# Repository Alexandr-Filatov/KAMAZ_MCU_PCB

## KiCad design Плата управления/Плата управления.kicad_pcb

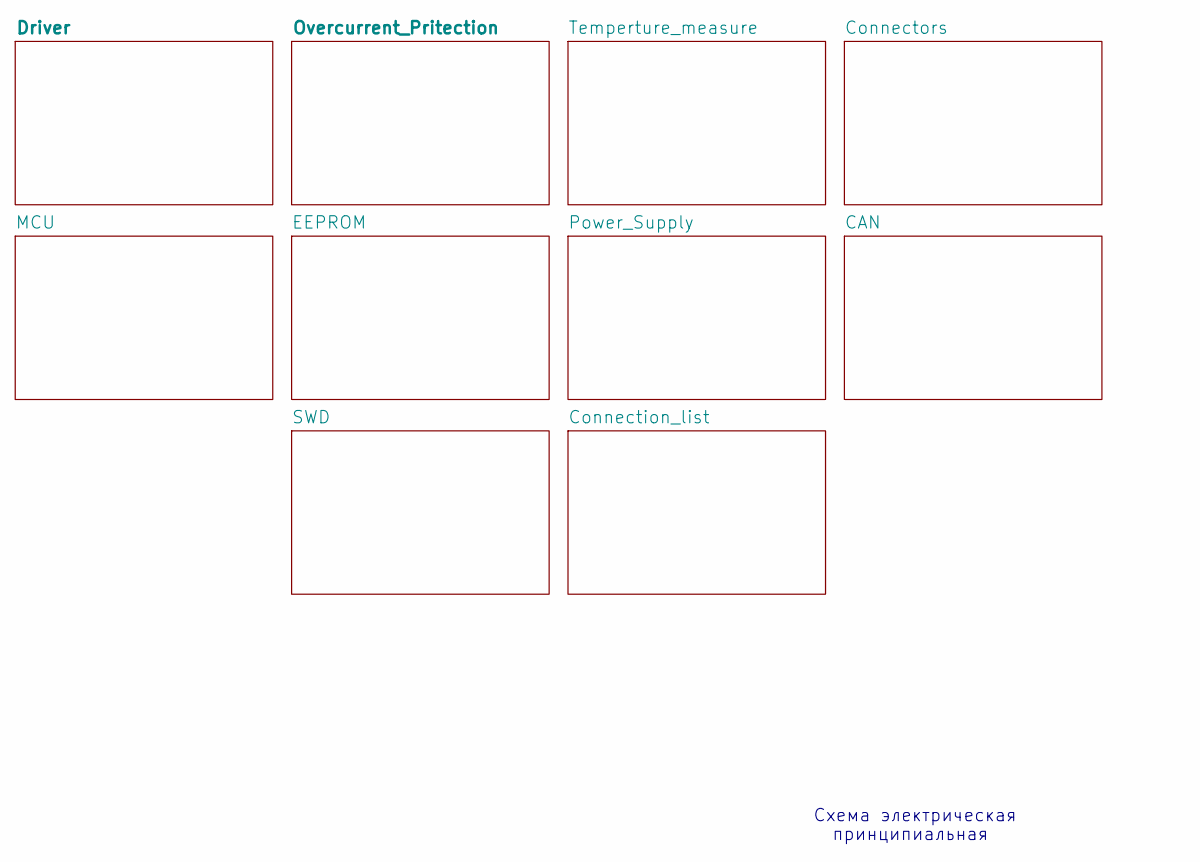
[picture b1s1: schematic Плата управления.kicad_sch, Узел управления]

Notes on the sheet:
принципиальная
Схема электрическая

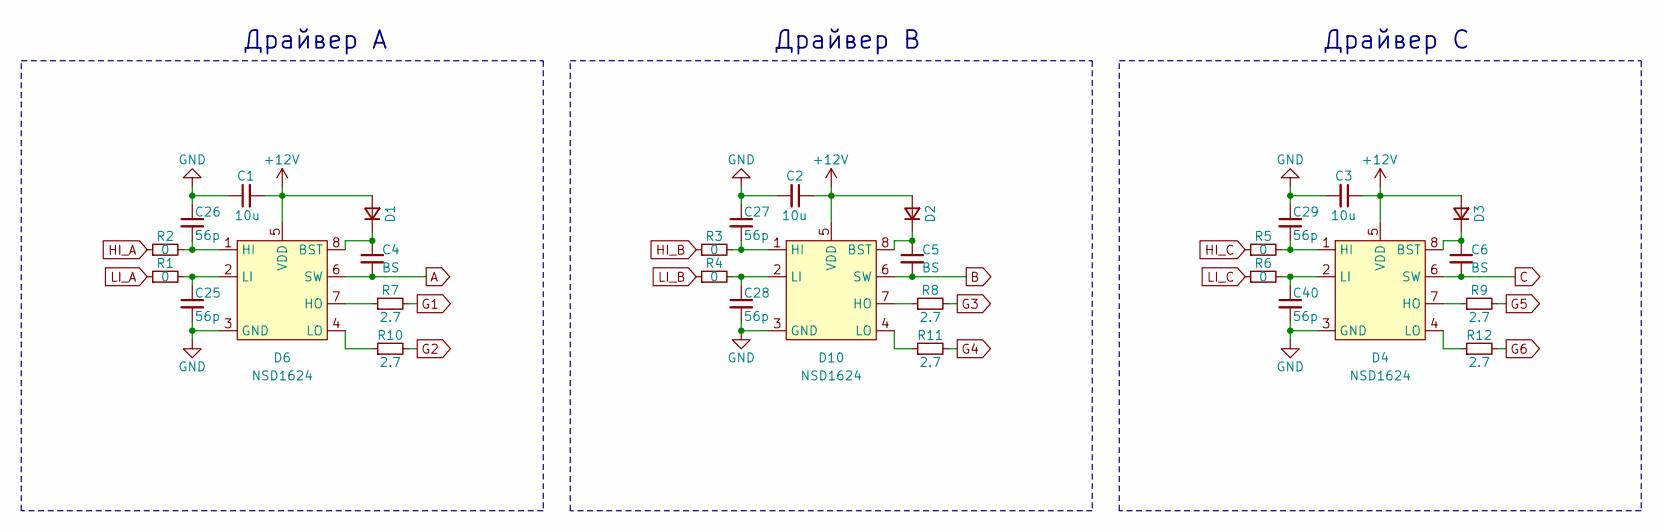
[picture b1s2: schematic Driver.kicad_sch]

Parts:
C1, C2, C3: 10u; C_0603_1608Metric_Pad1.08x0.95mm_HandSolder
C4, C5, C6: BS; C_0805_2012Metric_Pad1.18x1.45mm_HandSolder
C25, C26, C27, C28, C29, C40: 56p; C_0603_1608Metric_Pad1.08x0.95mm_HandSolder
D1, D2, D3: D_Small; D_SMA
D4, D6, D10: NSD1624; SOIC-8_3.9x4.9mm_P1.27mm
R1, R2, R3, R4, R5, R6: 0; R_0603_1608Metric_Pad0.98x0.95mm_HandSolder
R7, R8, R9, R10, R11, R12: 2.7; R_0805_2012Metric_Pad1.20x1.40mm_HandSolder

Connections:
+12V: C1.2, C2.1, C3.1, D1.2 (A), D2.2 (A), D3.2 (A), D4.5 (VDD), D6.5 (VDD), D10.5 (VDD); also elsewhere on the board
A: C4.2, D6.6 (SW); also elsewhere on the board
B: C5.2, D10.6 (SW); also elsewhere on the board
C: C6.2, D4.6 (SW); also elsewhere on the board
G1: R7.2; also elsewhere on the board
G2: R10.2; also elsewhere on the board
G3: R8.2; also elsewhere on the board
G4: R11.2; also elsewhere on the board
G5: R9.2; also elsewhere on the board
G6: R12.2; also elsewhere on the board
GND: C1.1, C2.2, C3.2, C25.2, C26.1, C27.1, C28.2, C29.1, C40.2, D4.3 (GND), D6.3 (GND), D10.3 (GND); also elsewhere on the board
HI_A: R2.1; also elsewhere on the board
HI_B: R3.1; also elsewhere on the board
HI_C: R5.1; also elsewhere on the board
LI_A: R1.1; also elsewhere on the board
LI_B: R4.1; also elsewhere on the board
LI_C: R6.1; also elsewhere on the board
unnamed: C4.1, D1.1 (K), D6.8 (BST)
unnamed: C6.1, D3.1 (K), D4.8 (BST)
unnamed: C29.2, D4.1 (HI), R5.2
unnamed: D4.7 (HO), R9.1
unnamed: C40.1, D4.2 (LI), R6.2
unnamed: D4.4 (LO), R12.1
unnamed: C26.2, D6.1 (HI), R2.2
unnamed: D6.7 (HO), R7.1
unnamed: C25.1, D6.2 (LI), R1.2
unnamed: D6.4 (LO), R10.1
unnamed: C5.1, D2.1 (K), D10.8 (BST)
unnamed: C27.2, D10.1 (HI), R3.2
unnamed: D10.7 (HO), R8.1
unnamed: C28.1, D10.2 (LI), R4.2
unnamed: D10.4 (LO), R11.1

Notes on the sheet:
Драйвер С
Драйвер А
Драйвер В

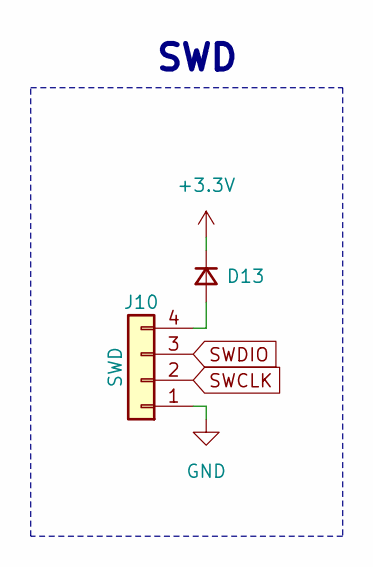
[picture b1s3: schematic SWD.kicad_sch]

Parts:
D13: D_Small; D_SOD-323_HandSoldering
J10: SWD; PinHeader_1x04_P2.54mm_Vertical

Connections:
+3.3V: D13.1 (K); also elsewhere on the board
GND: J10.1; also elsewhere on the board
unnamed: D13.2 (A), J10.4
SWCLK: J10.2; also elsewhere on the board
SWDIO: J10.3; also elsewhere on the board

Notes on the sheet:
SWD

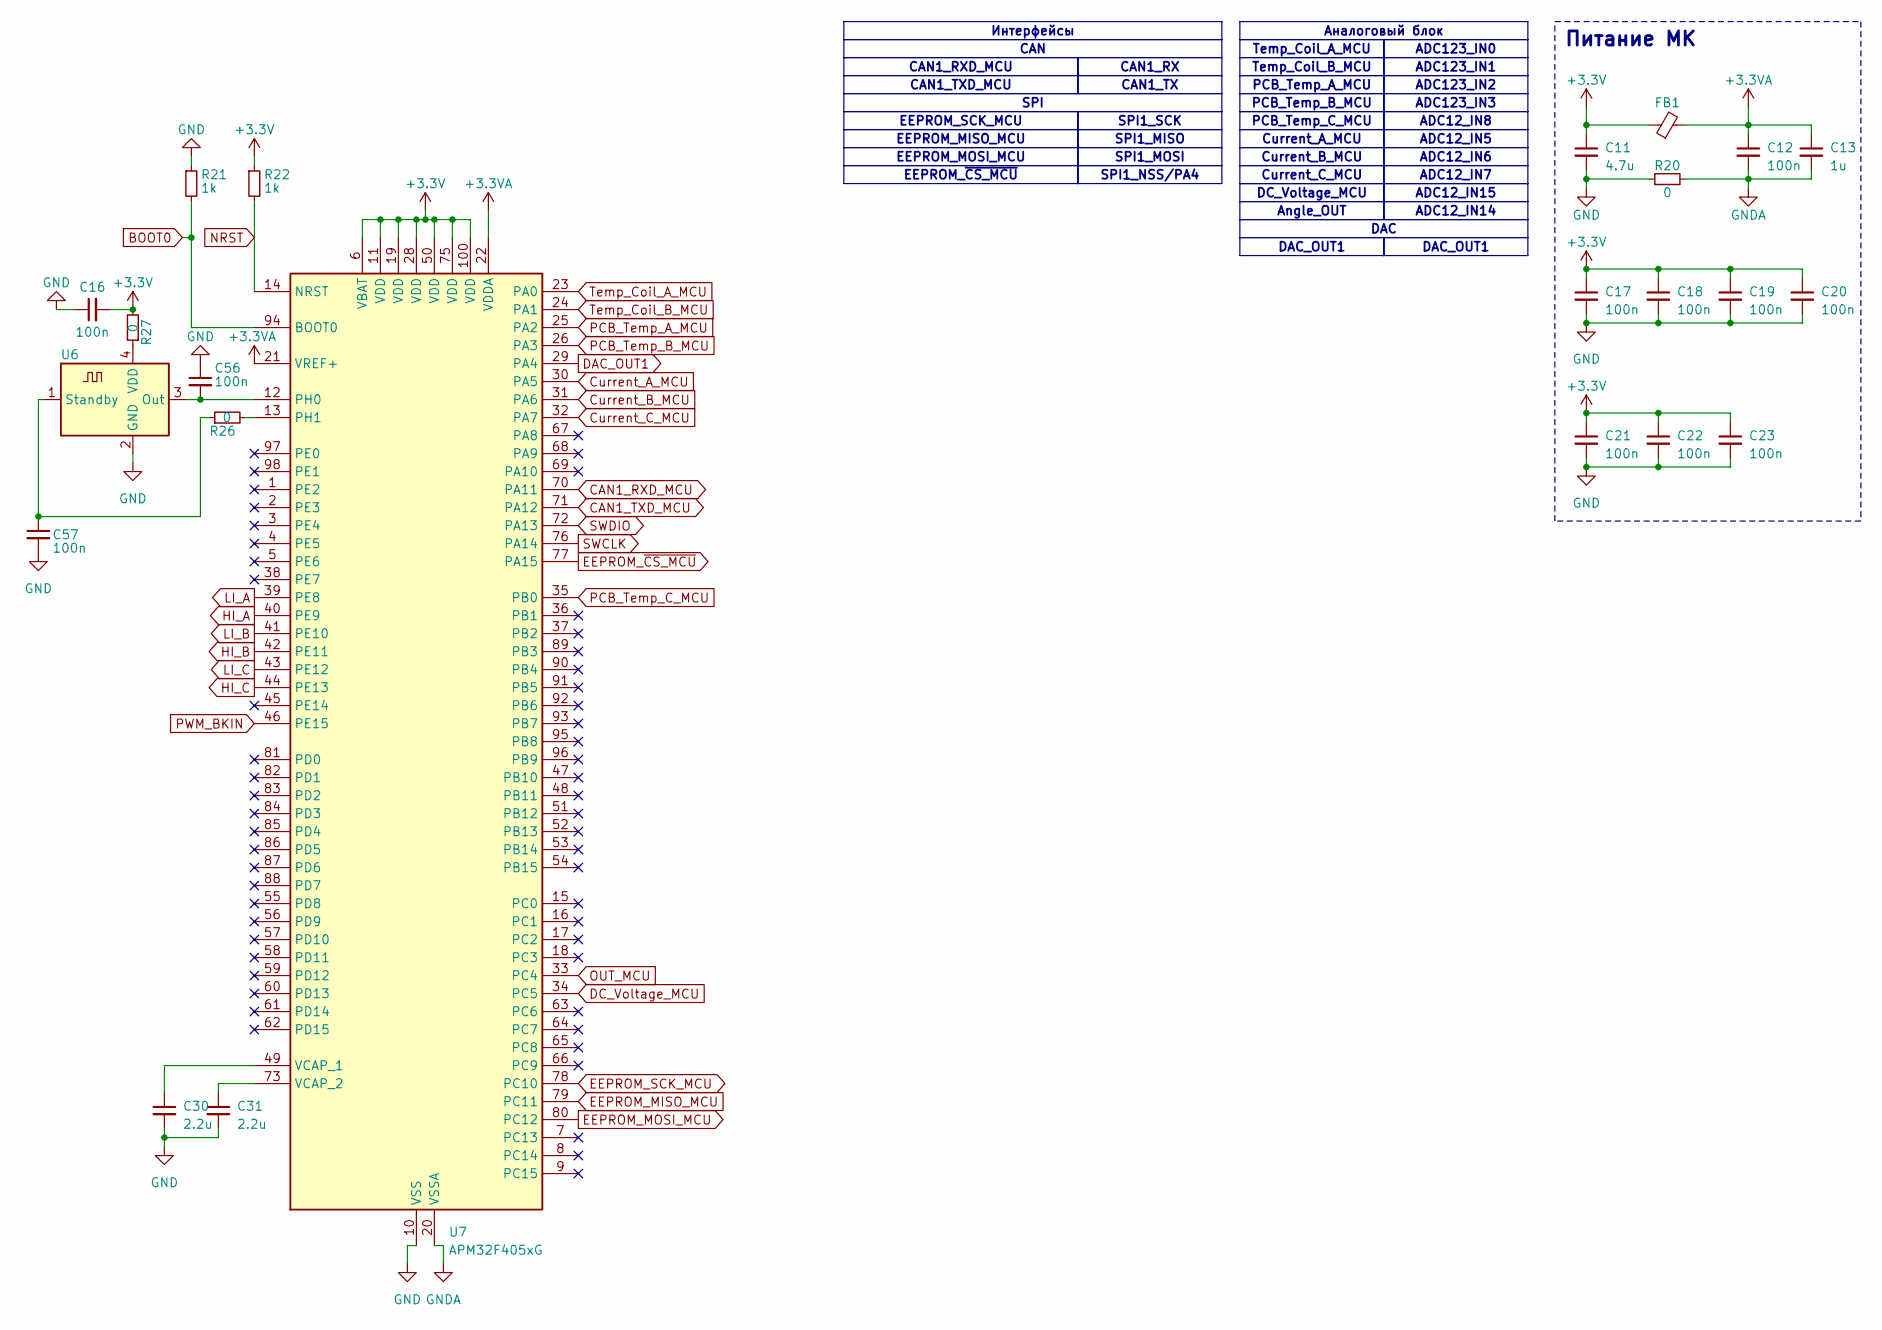
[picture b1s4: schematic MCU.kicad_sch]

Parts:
C11: 4.7u; C_0603_1608Metric_Pad1.08x0.95mm_HandSolder
C12, C16, C17, C18, C19, C20, C21, C22, C23, C56, C57: 100n; C_0603_1608Metric_Pad1.08x0.95mm_HandSolder
C13: 1u; C_0603_1608Metric_Pad1.08x0.95mm_HandSolder
C30, C31: 2.2u; C_0603_1608Metric_Pad1.08x0.95mm_HandSolder
FB1: BLM18KG102SH1D; L_0603_1608Metric_Pad1.05x0.95mm_HandSolder
R20, R26, R27: 0; R_0603_1608Metric_Pad0.98x0.95mm_HandSolder
R21, R22: 1k; R_0603_1608Metric_Pad0.98x0.95mm_HandSolder
U6: ASEMB-10; Oscillator_SMD_Abracon_ASE-4Pin_3.2x2.5mm_HandSoldering
U7: APM32F405xG; LQFP-100_14x14mm_P0.5mm

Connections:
+3.3V: C11.1, C16.2, C17.1, C18.1, C19.1, C20.1, C21.1, C22.1, C23.1, FB1.1, R22.1, R27.2, U7.6 (VBAT), U7.11 (VDD), U7.19 (VDD), U7.28 (VDD), U7.50 (VDD), U7.75 (VDD), U7.100 (VDD); also elsewhere on the board
BOOT0: R21.2, U7.94 (BOOT0)
CAN1_RXD_MCU: U7.70 (PA11); also elsewhere on the board
CAN1_TXD_MCU: U7.71 (PA12); also elsewhere on the board
Current_A_MCU: U7.30 (PA5); also elsewhere on the board
Current_B_MCU: U7.31 (PA6); also elsewhere on the board
Current_C_MCU: U7.32 (PA7); also elsewhere on the board
DAC_OUT1: U7.29 (PA4)
DC_Voltage_MCU: U7.34 (PC5); also elsewhere on the board
EEPROM_MISO_MCU: U7.79 (PC11); also elsewhere on the board
EEPROM_MOSI_MCU: U7.80 (PC12); also elsewhere on the board
EEPROM_SCK_MCU: U7.78 (PC10); also elsewhere on the board
EEPROM_~CS_MCU: U7.77 (PA15); also elsewhere on the board
GND: C11.2, C16.1, C17.2, C18.2, C19.2, C20.2, C21.2, C22.2, C23.2, C30.2, C31.2, C56.1, C57.2, R20.1, R21.1, U6.2 (GND), U7.10 (VSS), U7.27 (VSS), U7.74 (VSS), U7.99 (VSS); also elsewhere on the board
GNDA: C12.2, C13.2, R20.2, U7.20 (VSSA); also elsewhere on the board
HI_A: U7.40 (PE9); also elsewhere on the board
HI_B: U7.42 (PE11); also elsewhere on the board
HI_C: U7.44 (PE13); also elsewhere on the board
LI_A: U7.39 (PE8); also elsewhere on the board
LI_B: U7.41 (PE10); also elsewhere on the board
LI_C: U7.43 (PE12); also elsewhere on the board
NRST: R22.2, U7.14 (NRST)
NTC_A+: C12.1, C13.1, FB1.2, U7.21 (VREF+), U7.22 (VDDA); also elsewhere on the board
unnamed: C56.2, U6.3 (Out), U7.12 (PH0)
unnamed: C57.1, R26.1, U6.1 (Standby)
unnamed: R27.1, U6.4 (VDD)
unnamed: R26.2, U7.13 (PH1)
unnamed: C30.1, U7.49 (VCAP_1)
unnamed: C31.1, U7.73 (VCAP_2)
OUT_MCU: U7.33 (PC4); also elsewhere on the board
PCB_Temp_A_MCU: U7.25 (PA2); also elsewhere on the board
PCB_Temp_B_MCU: U7.26 (PA3); also elsewhere on the board
PCB_Temp_C_MCU: U7.35 (PB0); also elsewhere on the board
PWM_BKIN: U7.46 (PE15); also elsewhere on the board
SWCLK: U7.76 (PA14); also elsewhere on the board
SWDIO: U7.72 (PA13); also elsewhere on the board
Temp_Coil_A_MCU: U7.23 (PA0); also elsewhere on the board
Temp_Coil_B_MCU: U7.24 (PA1); also elsewhere on the board

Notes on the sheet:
EEPROM_MOSI_MCU
SPI1_MOSI
Angle_OUT
ADC123_IN0
DAC_OUT1
ADC12_IN15
CAN1_RXD_MCU
SPI1_MISO
CAN1_TX
SPI1_NSS/PA4
DC_Voltage_MCU
ADC12_IN5
EEPROM_~{CS_MCU}
ADC123_IN2
Current_C_MCU
CAN1_TXD_MCU
EEPROM_MISO_MCU
PCB_Temp_A_MCU
PCB_Temp_C_MCU
DAC
Temp_Coil_B_MCU
ADC12_IN14
Current_A_MCU
CAN
ADC12_IN6
Temp_Coil_A_MCU
ADC12_IN7
Аналоговый блок
SPI1_SCK
ADC123_IN3
ADC12_IN8
EEPROM_SCK_MCU
SPI
Current_B_MCU
CAN1_RX
PCB_Temp_B_MCU
ADC123_IN1
Интерфейсы
Питание МК

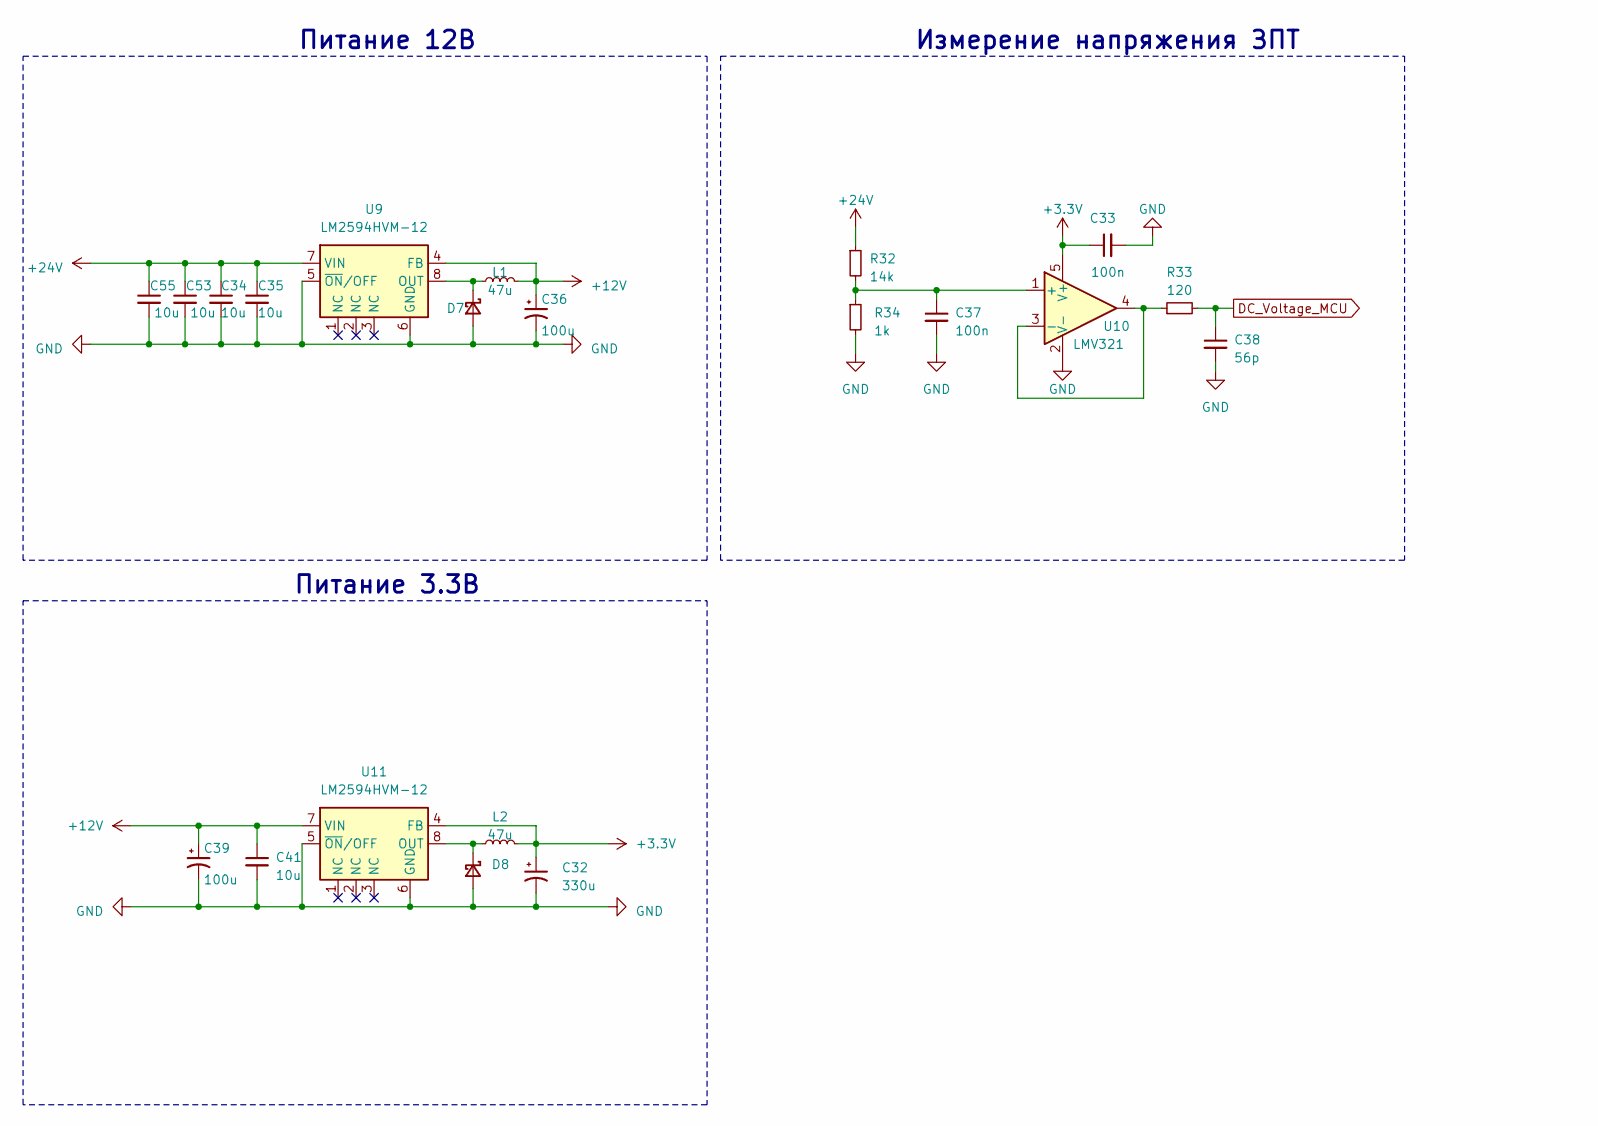
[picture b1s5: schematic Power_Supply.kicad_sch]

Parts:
C32: 330u; CP_EIA-7343-31_Kemet-D_Pad2.25x2.55mm_HandSolder
C33, C37: 100n; C_0603_1608Metric_Pad1.08x0.95mm_HandSolder
C34, C35, C41, C53, C55: 10u; C_1210_3225Metric_Pad1.33x2.70mm_HandSolder
C36, C39: 100u; CP_EIA-7343-43_Kemet-X_Pad2.25x2.55mm_HandSolder
C38: 56p; C_0603_1608Metric_Pad1.08x0.95mm_HandSolder
D7, D8: MBRA320; D_SMA
L1, L2: 47u; C_2220_5650Metric_Pad1.97x5.40mm_HandSolder
R32: 14k; R_0603_1608Metric_Pad0.98x0.95mm_HandSolder
R33: 120; R_0603_1608Metric_Pad0.98x0.95mm_HandSolder
R34: 1k; R_0603_1608Metric_Pad0.98x0.95mm_HandSolder
U9, U11: LM2594HVM-12; SOIC-8_3.9x4.9mm_P1.27mm
U10: LMV321; SOT-23-5_HandSoldering

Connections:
+3.3V: C32.1, C33.1, L2.2, U10.5 (V+), U11.4 (FB); also elsewhere on the board
+12V: C36.1, C39.1, C41.1, L1.2, U9.4 (FB), U11.7 (VIN); also elsewhere on the board
+24V: C34.1, C35.1, C53.1, C55.1, R32.1, U9.7 (VIN); also elsewhere on the board
DC_Voltage_MCU: C38.1, R33.2; also elsewhere on the board
GND: C32.2, C33.2, C34.2, C35.2, C36.2, C37.2, C38.2, C39.2, C41.2, C53.2, C55.2, D7.2 (A), D8.2 (A), R34.2, U9.5 (~ON/OFF), U9.6 (GND), U10.2 (V-), U11.5 (~ON/OFF), U11.6 (GND); also elsewhere on the board
unnamed: D7.1 (K), L1.1, U9.8 (OUT)
unnamed: D8.1 (K), L2.1, U11.8 (OUT)
unnamed: C37.1, R32.2, R34.1, U10.1 (+)
unnamed: R33.1, U10.3 (-), U10.4

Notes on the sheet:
Питание 3.3В
Измерение напряжения ЗПТ
Питание 12В

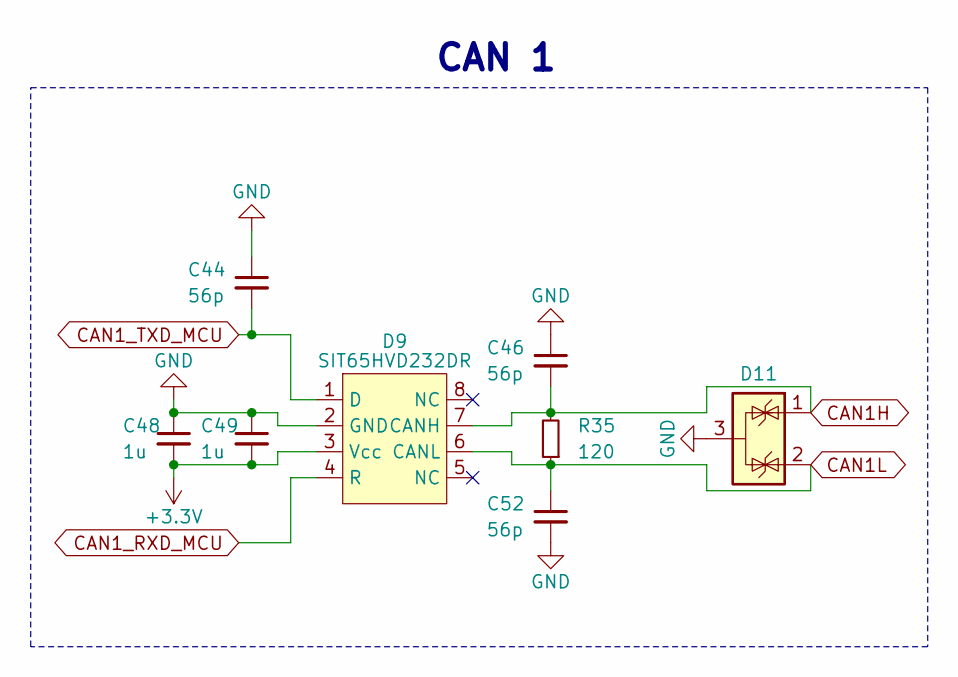
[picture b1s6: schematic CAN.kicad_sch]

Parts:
C44, C46, C52: 56p; C_0603_1608Metric_Pad1.08x0.95mm_HandSolder
C48, C49: 1u; C_0603_1608Metric_Pad1.08x0.95mm_HandSolder
D9: SIT65HVD232DR; SOIC-8_3.9x4.9mm_P1.27mm
D11: PESD2CAN; SOT-23
R35: 120; R_0603_1608Metric_Pad0.98x0.95mm_HandSolder

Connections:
+3.3V: C48.2, C49.2, D9.3 (Vcc); also elsewhere on the board
CAN1H: C46.2, D9.7 (CANH), D11.1 (K), R35.2; also elsewhere on the board
CAN1L: C52.1, D9.6 (CANL), D11.2 (K), R35.1; also elsewhere on the board
CAN1_RXD_MCU: D9.4 (R); also elsewhere on the board
CAN1_TXD_MCU: C44.2, D9.1 (D); also elsewhere on the board
GND: C44.1, C46.1, C48.1, C49.1, C52.2, D9.2 (GND), D11.3 (A); also elsewhere on the board

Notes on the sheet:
CAN 1

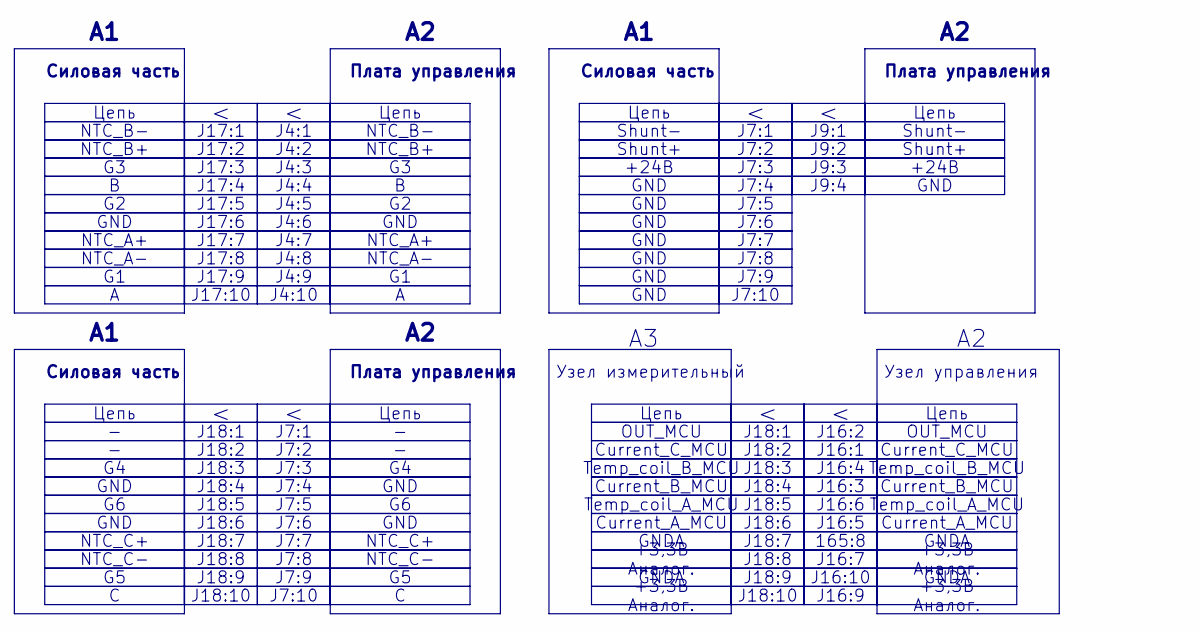
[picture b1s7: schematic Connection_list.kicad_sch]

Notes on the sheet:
GND
J16:4
GNDA
J7:10
J18:2
J7:6
J7:6
J18:8
Temp_coil_B_MCU
J7:4
Shunt+
J18:7
J17:8
J4:6
NTC_C+
J7:3
Цепь
J7:1
J16:7
+24В
J18:10
J7:9
J18:3
J7:7
OUT_MCU
J7:3
J18:8
NTC_B-
J18:4
J7:7
J18:6
NTC_A+
J9:3
Shunt-
+3,3В Аналог.
J4:10
Temp_coil_A_MCU
J18:3
J18:1
J7:2

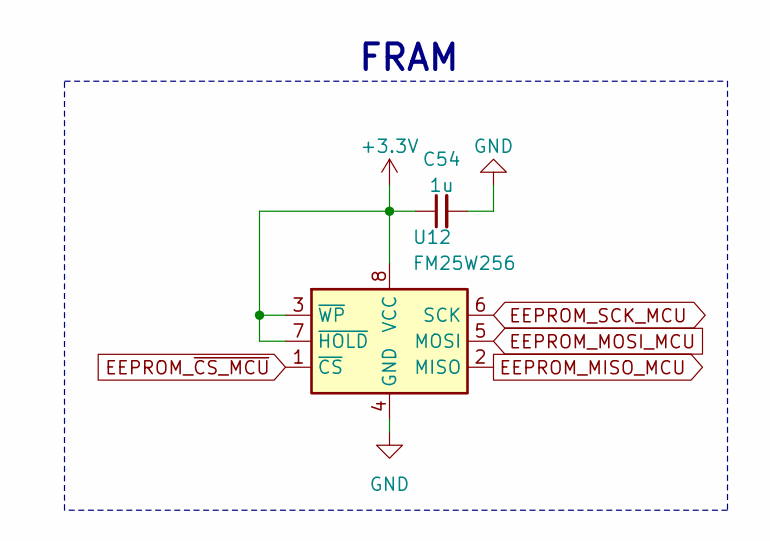
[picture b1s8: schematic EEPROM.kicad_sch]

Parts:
C54: 1u; C_0603_1608Metric_Pad1.08x0.95mm_HandSolder
U12: FM25W256; SOIC-8_3.9x4.9mm_P1.27mm

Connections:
+3.3V: C54.1, U12.3 (~WP), U12.7 (~HOLD), U12.8 (VCC); also elsewhere on the board
EEPROM_MISO_MCU: U12.2 (MISO); also elsewhere on the board
EEPROM_MOSI_MCU: U12.5 (MOSI); also elsewhere on the board
EEPROM_SCK_MCU: U12.6 (SCK); also elsewhere on the board
EEPROM_~CS_MCU: U12.1 (~CS); also elsewhere on the board
GND: C54.2, U12.4 (GND); also elsewhere on the board

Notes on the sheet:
FRAM

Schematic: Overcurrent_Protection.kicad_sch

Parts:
C7, C8: 100n; C_0603_1608Metric_Pad1.08x0.95mm_HandSolder
C9, C10: 56p; C_0603_1608Metric_Pad1.08x0.95mm_HandSolder
R13: 649; R_0603_1608Metric_Pad0.98x0.95mm_HandSolder
R14: 1k; R_0603_1608Metric_Pad0.98x0.95mm_HandSolder
R15, R16: 120; R_0603_1608Metric_Pad0.98x0.95mm_HandSolder
U4: LMV7239M5; SOT-23-5_HandSoldering
U5: AD8418A; SOIC-8_3.9x4.9mm_P1.27mm

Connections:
+3.3V: C7.1, C8.1, R13.1, U4.5 (V+), U5.6 (V+); also elsewhere on the board
GND: C7.2, C8.2, C9.2, C10.2, R14.2, U4.2 (V-), U5.2 (GND), U5.3 (REF2), U5.7 (REF1); also elsewhere on the board
unnamed: R15.1, U4.1
unnamed: R16.2, U5.5
unnamed: C10.1, R16.1, U4.3 (+)
unnamed: R13.2, R14.1, U4.4 (-)
PWM_BKIN: C9.1, R15.2; also elsewhere on the board
Shunt+: U5.8 (+); also elsewhere on the board
Shunt-: U5.1 (-); also elsewhere on the board

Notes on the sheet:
Защита от КЗ

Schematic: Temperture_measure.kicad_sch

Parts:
C14, C24, C42, C43, C47, C50: 100n; C_0603_1608Metric_Pad1.08x0.95mm_HandSolder
C15, C45, C51: 56p; C_0603_1608Metric_Pad1.08x0.95mm_HandSolder
R17, R18, R19: 120; R_0603_1608Metric_Pad0.98x0.95mm_HandSolder
R23, R24, R25: 10k; R_0603_1608Metric_Pad0.98x0.95mm_HandSolder
U1, U2, U8: LMV321; SOT-23-5_HandSoldering

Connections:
GNDA: C14.1, C15.2, C24.2, C42.1, C43.2, C45.2, C47.1, C50.2, C51.2, R23.1, R24.1, R25.1, U1.2 (V-), U2.2 (V-), U8.2 (V-); also elsewhere on the board
NTC_A+: C24.1, C43.1, C50.1, U1.5 (V+), U2.5 (V+), U8.5 (V+); also elsewhere on the board
NTC_A-: C14.2, R23.2, U8.1 (+); also elsewhere on the board
NTC_B-: C42.2, R24.2, U1.1 (+); also elsewhere on the board
NTC_C-: C47.2, R25.2, U2.1 (+); also elsewhere on the board
unnamed: R18.1, U1.3 (-), U1.4
unnamed: R19.1, U2.3 (-), U2.4
unnamed: R17.1, U8.3 (-), U8.4
PCB_Temp_A_MCU: C15.1, R17.2; also elsewhere on the board
PCB_Temp_B_MCU: C45.1, R18.2; also elsewhere on the board
PCB_Temp_C_MCU: C51.1, R19.2; also elsewhere on the board

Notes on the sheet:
Температура силовой платы A
Температура силовой платы B
Температура силовой платы C

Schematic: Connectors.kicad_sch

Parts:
J1: A; Hole_9mm
J2: B; Hole_9mm
J3: C; Hole_9mm
J4, J7: Conn_01x10; PinHeader_1x10_P1.27mm_Vertical
J5, J11, J12, J13, J14, J15: C; Wire_one
J6, J8: Conn_01x02; PinHeader_1x02_P1.27mm_Vertical
J9: Conn_01x04; PinHeader_1x04_P1.27mm_Vertical
J16: Conn_02x05_Odd_Even; PinHeader_2x05_P1.27mm_Vertical

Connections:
+24V: J9.3; also elsewhere on the board
A: J4.10; also elsewhere on the board
B: J4.4; also elsewhere on the board
C: J7.10; also elsewhere on the board
CAN1H: J5.1, J13.1; also elsewhere on the board
CAN1L: J11.1, J14.1; also elsewhere on the board
Current_A_MCU: J16.5; also elsewhere on the board
Current_B_MCU: J16.3; also elsewhere on the board
Current_C_MCU: J16.1; also elsewhere on the board
G1: J4.9; also elsewhere on the board
G2: J4.5; also elsewhere on the board
G3: J4.3; also elsewhere on the board
G4: J7.3; also elsewhere on the board
G5: J7.9; also elsewhere on the board
G6: J7.5; also elsewhere on the board
GND: J4.6, J7.4, J7.6, J9.4, J12.1, J15.1; also elsewhere on the board
GNDA: J16.8, J16.10; also elsewhere on the board
NTC_A+: J4.2, J4.7, J7.7, J16.7, J16.9; also elsewhere on the board
NTC_A-: J4.8; also elsewhere on the board
NTC_B-: J4.1; also elsewhere on the board
NTC_C-: J7.8; also elsewhere on the board
OUT_MCU: J16.2; also elsewhere on the board
Shunt+: J9.2; also elsewhere on the board
Shunt-: J9.1; also elsewhere on the board
Temp_Coil_A_MCU: J16.6; also elsewhere on the board
Temp_Coil_B_MCU: J16.4; also elsewhere on the board

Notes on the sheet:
Фазные разъёмы
Разъём платы датчиков
Наружний разъём
Разъём платы силовой

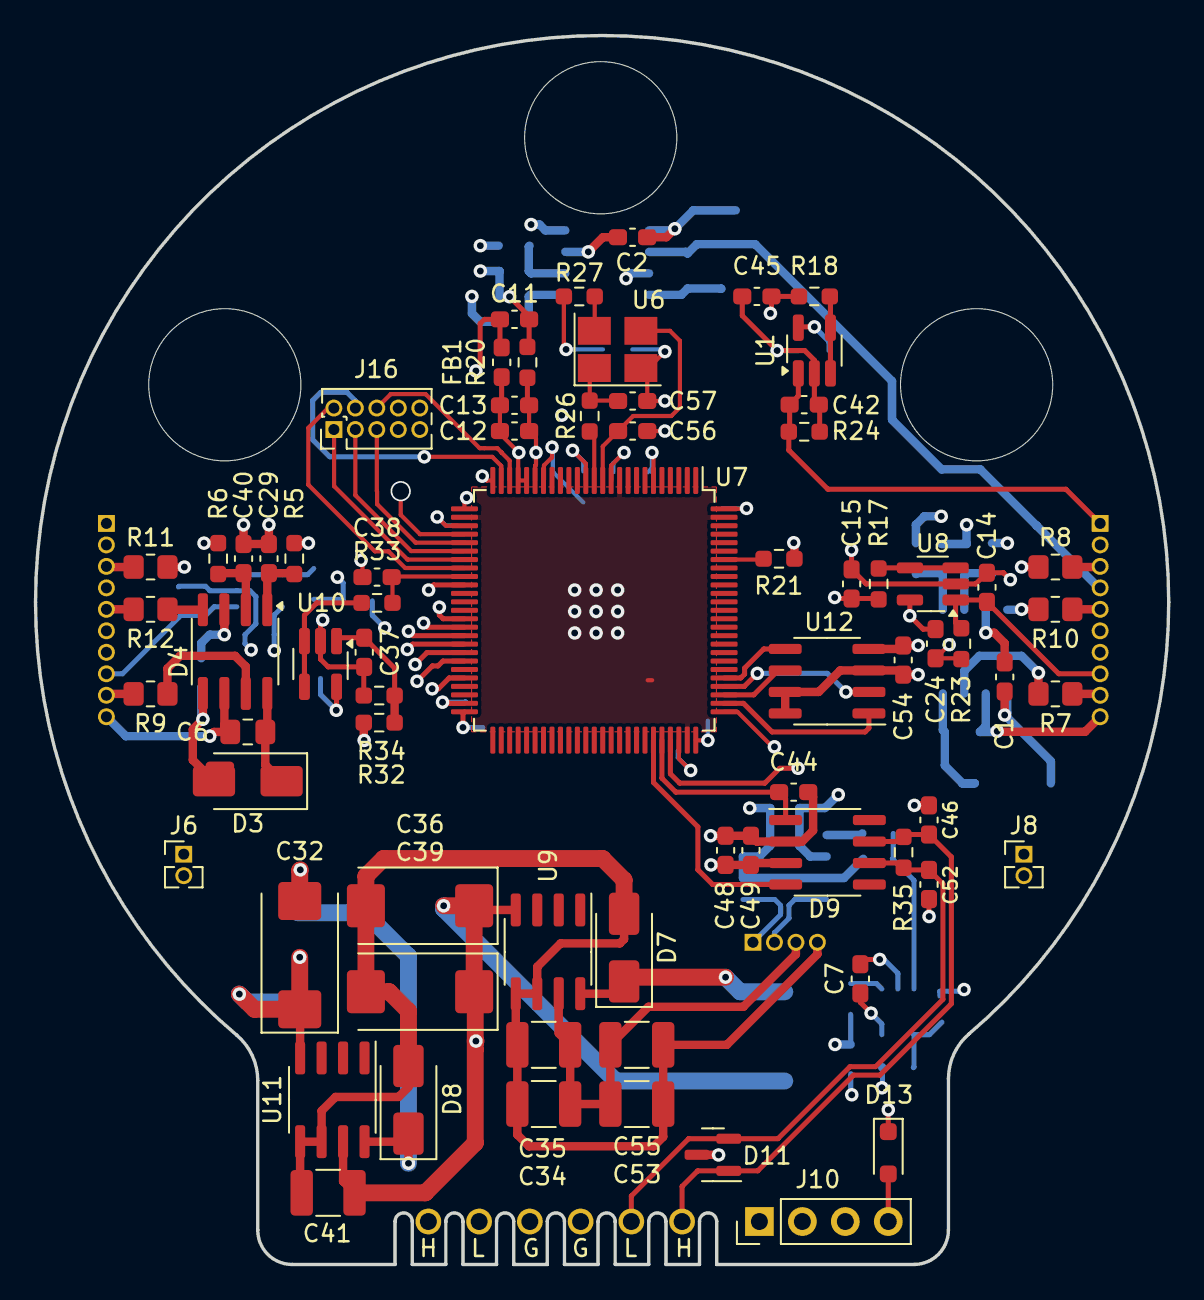
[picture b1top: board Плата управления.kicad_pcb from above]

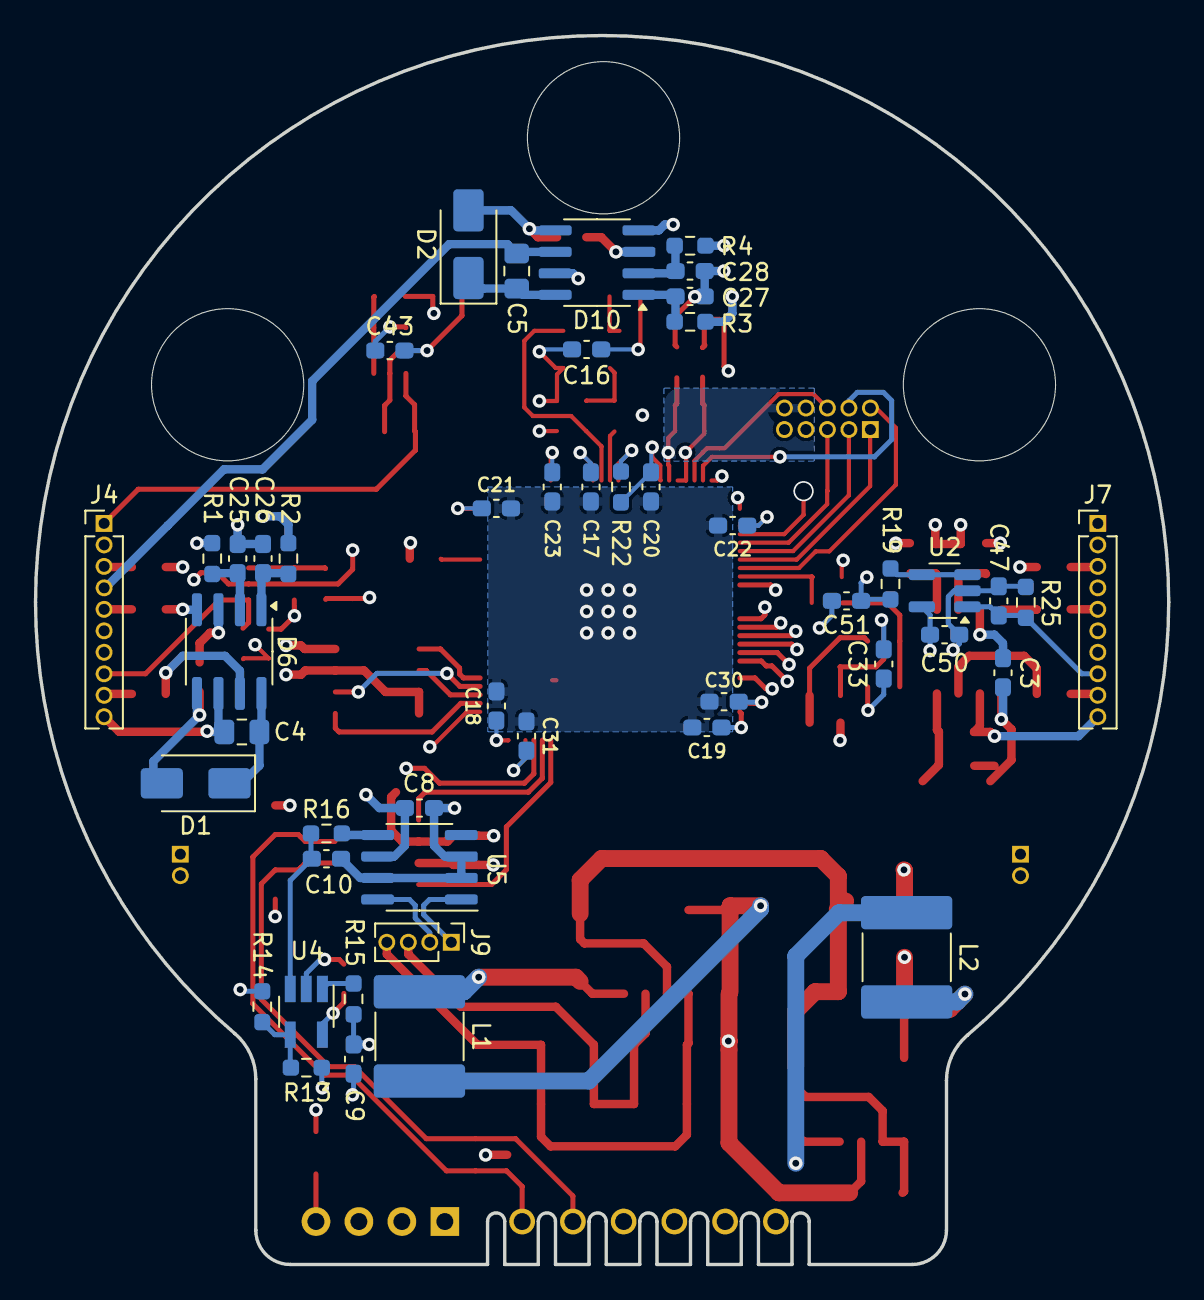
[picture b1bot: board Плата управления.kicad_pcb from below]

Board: 6 copper layers, 67.0 x 72.7 mm, 129 parts (48 on the bottom side), 82 nets.

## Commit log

2023-11-16 Нулевой вариант
2023-11-16 Питание с (lib_symbols
2023-11-16 Питанипе с TPS55165QPWPRQ1
2023-11-18 Поенял усилитель измерительный AD8210 на automotive исполнение INA283AID
2023-11-18 Заменил датчик положения ротора на NSM3012
2023-11-18 Добавил 3.3В CAN SN65HVD232
2023-11-18 Добавил питание 12В в automotive испорлнении и 3.3В
2023-11-19 Добавил питание MCU и кварц на 8Мгц
2023-11-19 Привел в порядок схему
2023-11-19 Расставил драйвера
2023-11-21 Добавил EEPROM
2023-11-22 Расставил компоненты по плате
2023-11-26 Изменил контур под новую крышку
2023-11-29 Добавил разъёмы под интерфейсы
2023-12-01 Новый контур платы
2023-12-03 Заменил разъём под силовую плату
2023-12-05 Изменил межплатный разъем
2023-12-05 Разделил аналоговое и цифровое питание
2023-12-11 Редактировал схему
2023-12-12 Финальная доработка
2023-12-12 Ещё нужно доработать
2023-12-15 Собираю документацию
2023-12-17 Добавил документы
2023-12-17 Добавил все документы
2023-12-24 Версия под отчёт
2024-05-16 Версия в производство 1.0
2024-05-16 Поправил посадочное место LMV7239M5
2024-05-16 Поправил посадочное место LMV321
2024-05-16 Исправил RX и TX у шины RS485 и разъединил ножки управления шиной
2024-05-16 Изменил разъём с 2.54мм на 2.0мм
2024-07-28 Zero commit
2024-08-01 VER2.0
2024-08-12 Добавил NTC обработку
2024-09-25 Новые драйвера и разъёмы
2024-09-26 Развел все длорожки
2024-09-29 Добавил разъёмф для крепления
2024-09-30 Добавил модель плты
2024-10-01 Добавил все в BOM
2024-10-01 Примерил разъёмы межплатные
2024-10-02 Добавил съемные разъемы
2024-10-03 Отправил на проверку в резонит
2024-12-02 Изменения: добавил папку с отчетностью
